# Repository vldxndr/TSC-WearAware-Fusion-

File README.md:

# InkTime - Smartwatch Project Technical Documentation

## 1. Overview
InkTime is an ultra-low-power open-hardware smartwatch designed around the nRF52840 SoC and a 1.54" E-paper display. The project focuses on extreme battery longevity, utilizing a high-efficiency dual-stage power supply and hardware-level power gating to achieve a standby target of 30 days or more.

---

## 2. System Architecture

### 2.1 Block Diagram
The system utilizes a dual-stage power topology to maximize battery discharge efficiency.

    [ USB Type-C ]     [ LiPo Battery (250mAh) ]
           | 5V VBUS          |
           v                  | BAT
    +---------------+         v
    |    BQ25180    |<--+ [MAX17048]
    |  (Charger IC) |   | (Fuel Gauge)
    +---------------+   |     |
           | VSYS       +-----+ I2C
           v                  v
    +---------------+      +-------------+
    |    RT6160     |      |             |
    | (Buck-Boost)  |      |  nRF52840   |
    +---------------+      |     MCU     |
           | 3.3V (VDD_3V3)|  (Control   |
           | System Rail   |    Hub)     |
           |               |             |
    +------+---------------+------+------+
    |      |               |      |
    |      v               |      |
    |  +-------------+     |      | SPI
    |  | PFET Switch |<--GPIO-----+      v
    |  +------+------+     |  +-------------+
    |      | VEPD          |  | 1.54" E-paper|
    |      v               |  |   Display   |
    |  +-------------+     |  +-------------+
    |  | [Display]   |     |
    |  +-------------+     | I2C Bus
    |                      |
    +---I2C==> [ BMA423 Accel ]
    |                      |
    +---I2C==> [ DRV2605L Driver ] --> [ Vibration Motor ]
    |
    |          [ PCB Antenna ] <--> [ BLE RF ]
    |
    +---GPIO-> [ User Buttons ]

---

## 3. Bill Of Materials (BOM)

| Designator | Component | Package | Manufacturer | Description |
| :--- | :--- | :--- | :--- | :--- |
| U1 | nRF52840 | aQFN-73 | Nordic Semi | SoC Bluetooth 5.0 |
| IC1 | BQ25180Y | DSBGA-8 | Texas Inst. | Li-Ion Charger w/ Power Path |
| IC9 | RT6160AWSC | WLCSP-15 | Richtek | 3.3V Buck-Boost Regulator |
| IC3 | BMA423 | LGA-12 | Bosch | Triaxial Accelerometer |
| U3 | MAX17048 | TDFN-8 | Maxim/ADI | 1-Cell Fuel Gauge |
| ANT1 | 2450AT18B100E| 1.4mm | Johanson | 2.45GHz Chip Antenna |
| J1 | 503480-2400 | FPC-24 | Molex | 0.5mm Pitch FPC Connector |
| J4 | KH-TYPE-C-16P| SMT | Kinghelm | USB Type-C 16-pin |
| Q3 | SI1308EDL | SOT-323 | Vishay | P-Channel PFET (Power Gate) |
| D3 | USBLC6-2 | SOT-23-6 | STMicro | ESD Protection |

---

## 4. Hardware Implementation Details

### 4.1 Power Management Strategy
The BQ25180 handles LiPo charging and provides the VSYS rail. This rail feeds the RT6160 Buck-Boost converter, which maintains a stable 3.3V output. This configuration is critical for longevity, as the Buck-Boost can maintain regulation even when the battery voltage drops below 3.3V, effectively utilizing the entire discharge curve of the LiPo cell.

### 4.2 Display Power Gating
To minimize parasitic leakage during deep sleep, the E-paper power rail (VEPD) is controlled via a SI1308EDL PFET high-side switch. The MCU toggles this switch via P1.01, physically disconnecting the display logic and charge pump from the power rail when no refresh cycle is active.

### 4.3 Haptic and Motion Sensing
* DRV2605L: Provides I2C-controlled haptic feedback for ERM/LRA motors with integrated waveform libraries.
* BMA423: Low-power accelerometer used for step counting and gesture recognition. It is configured to wake the MCU via a hardware interrupt on P0.08.

---

## 5. Pinout Mapping (nRF52840)

### 5.1 Communication Interfaces
* I2C (SDA/SCL): P0.06 / P0.07 (Shared bus for Charger, Fuel Gauge, Accel, and Haptics).
* SPI (Display): P0.02 (SCK), P0.03 (MOSI), P0.05 (CS), P0.15 (DC), P0.16 (RST).

### 5.2 GPIO Control Lines
* Display Busy: P0.17 (Input - monitors refresh state).
* Power Control: P1.01 (Output - PFET Enable).
* Haptic Enable: P0.12 (Output - DRV2605L EN).
* BMA Interrupt: P0.08 (Input - Motion wake-up).
* Battery Alert: P0.10 (Input - Fuel Gauge alert).
* Charger Interrupt: P0.11 (Input - Charging state change).

---

## 6. Layout Guidelines

### 6.1 RF Section
* The path from U1 Pin 55 (ANT) to ANT1 must be as short as possible.
* Maintain a 50-ohm impedance-controlled trace.
* Implement a ground keep-out zone on all layers directly beneath the ANT1 chip antenna.

### 6.2 Power Integrity
* Place the 0.47uH inductor (L7) and decoupling capacitors (22uF/10uF) as close as possible to the RT6160 (IC9) pins.
* Use wide traces for VBUS, VSYS, and VDD_3V3 to minimize voltage drops.

### 6.3 Grounding
* Utilize a solid ground plane on Layer 2.
* Stitch ground planes with multiple vias, especially near decoupling capacitors and the MCU thermal pad.

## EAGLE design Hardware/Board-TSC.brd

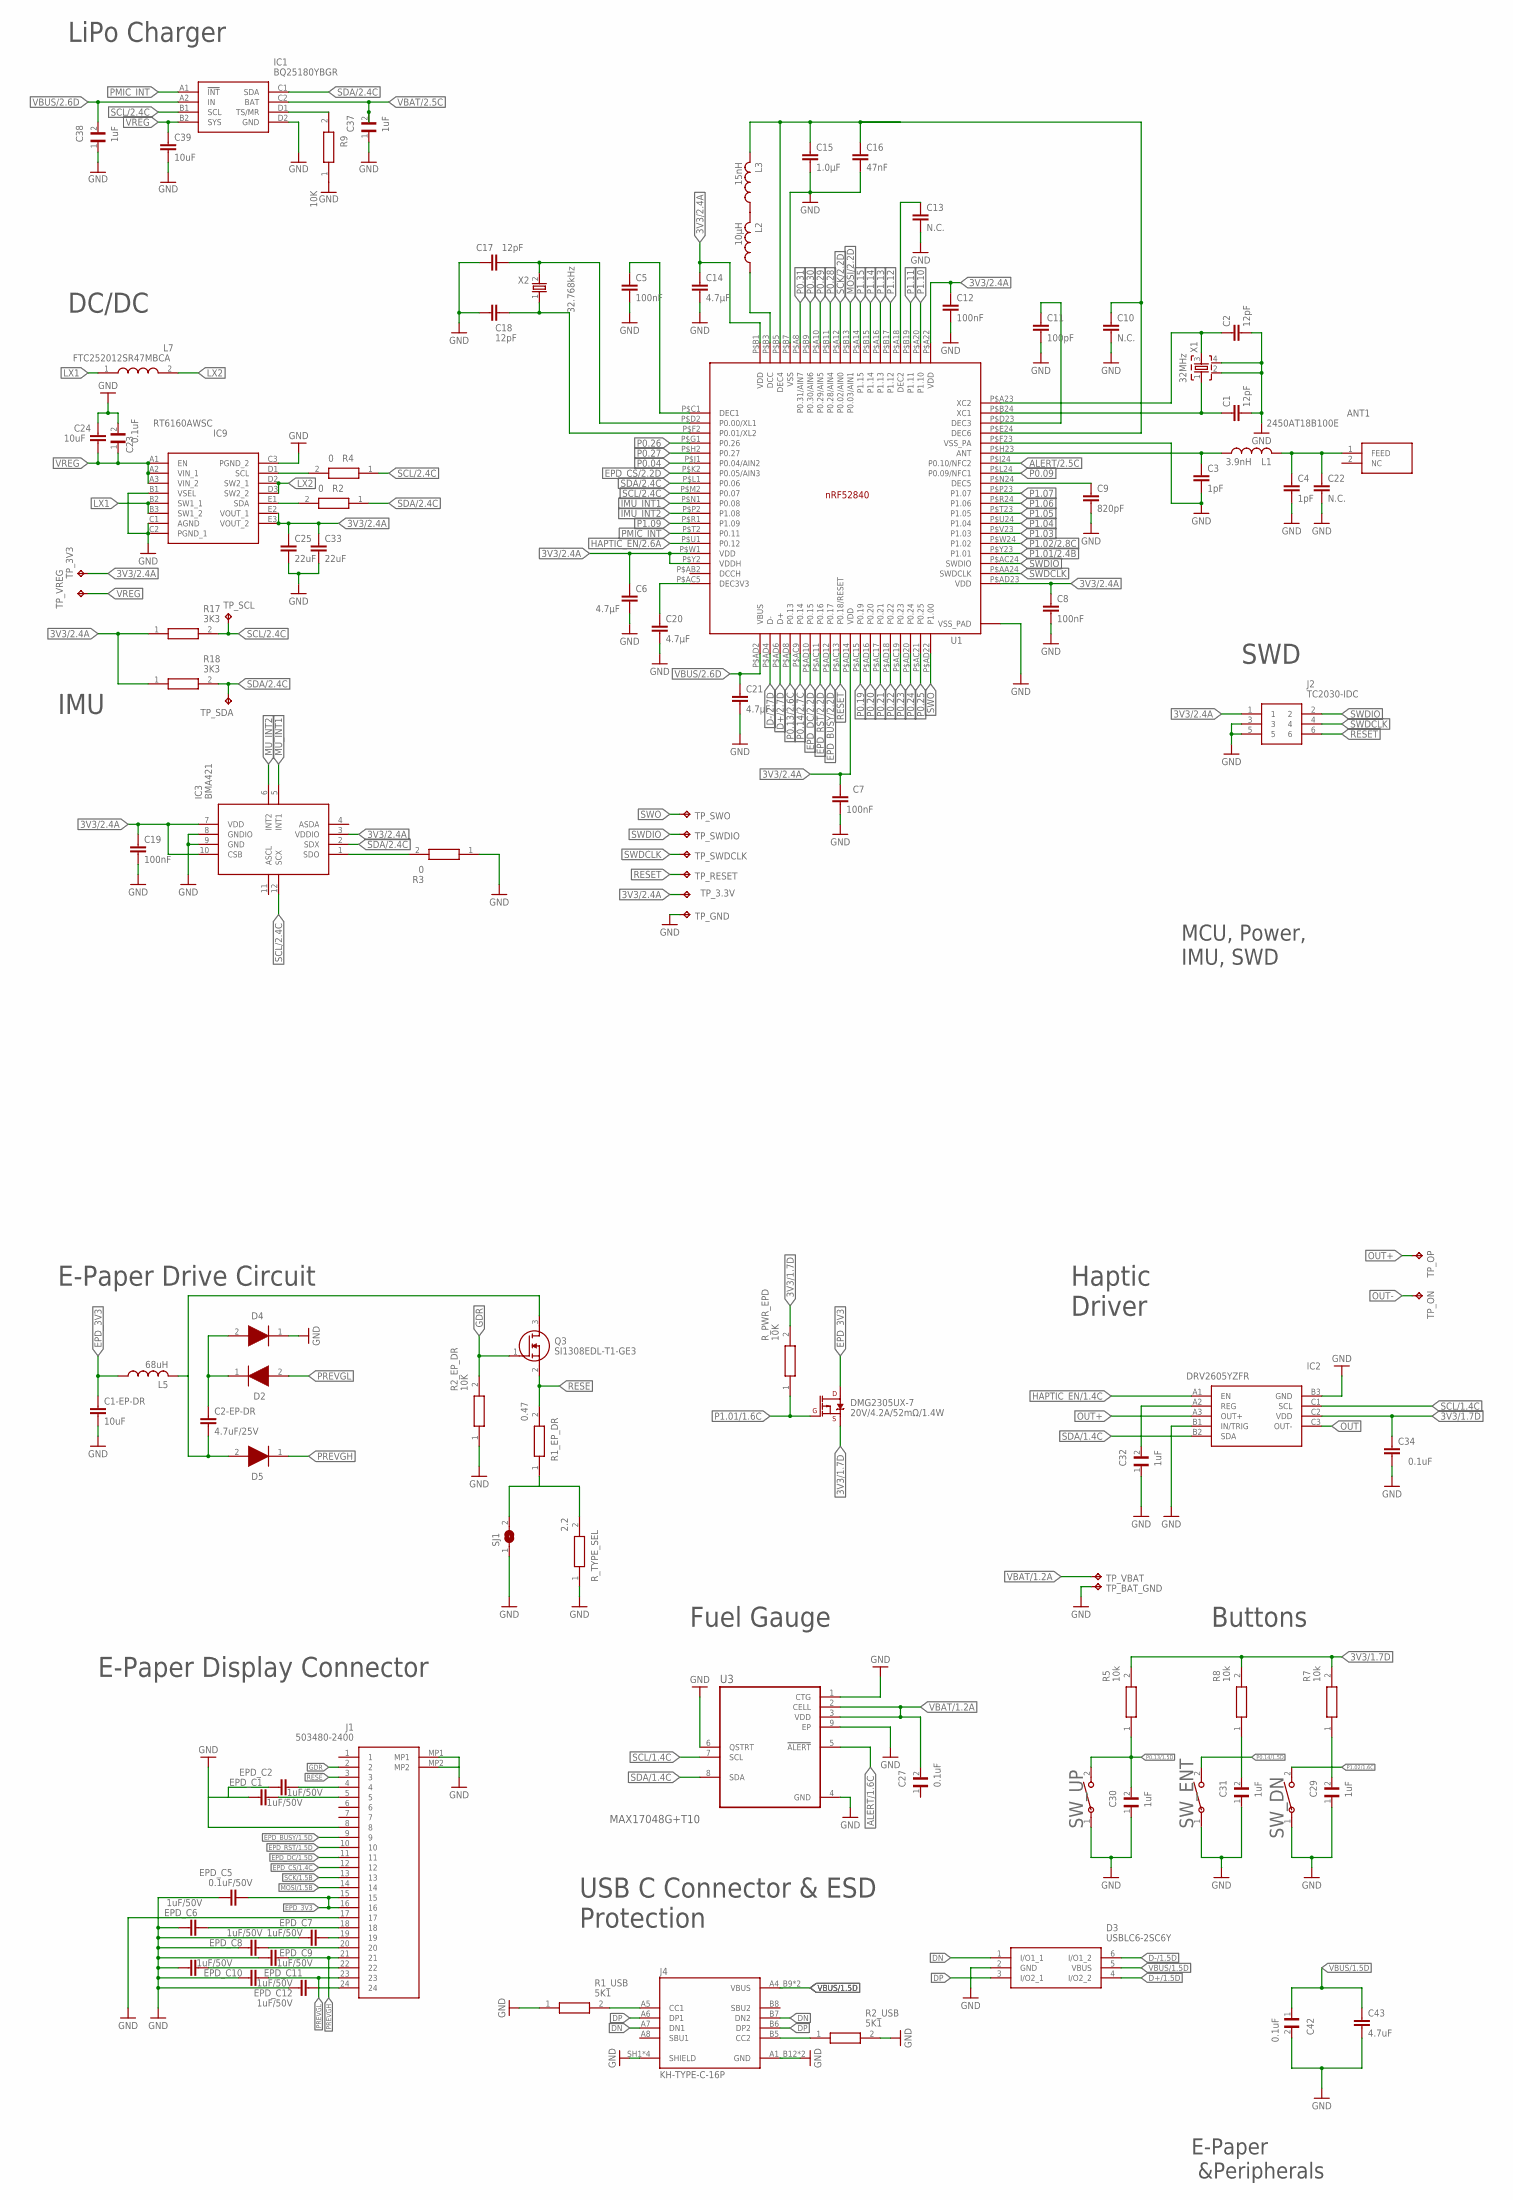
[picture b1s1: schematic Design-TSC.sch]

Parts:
ANT1: 2450AT18B100E; 2450AT18B100E_ANTC3216X140N
C1, C2, C17, C18: 12pF; NORDIC_NRF_3_RESC0201_L
C1-EP-DR, C39: 10uF; NORDIC_NRF_3_RESC0201_L
C2-EP-DR: 4.7uF/25V; NORDIC_NRF_3_RESC0201_L
C3, C4: 1pF; NORDIC_NRF_3_RESC0201_L
C5, C7, C8, C12, C19: 100nF; NORDIC_NRF_3_RESC0201_L
C6: 4.7µF; NORDIC_NRF_3_RESC0201_L
C9: 820pF; NORDIC_NRF_3_RESC0201_L
C10, C13, C22: N.C.; NORDIC_NRF_3_RESC0201_L
C11: 100pF; NORDIC_NRF_3_RESC0201_L
C14, C20, C21: 4.7µF; ESP32_C6_LIBRARY_1_ESP32_WROVER_EAGLE-LTSPICE_C0402
C15: 1.0µF; NORDIC_NRF_3_RESC0201_L
C16: 47nF; NORDIC_NRF_3_RESC0201_L
C23, C27, C42: 0.1uF; GRM011R60J152KE01L_2_CAPC0201X13N
C24: 10uF; ESP32_C6_LIBRARY_1_ESP32_WROVER_EAGLE-LTSPICE_C0402
C25, C33: 22uF; ESP32_C6_LIBRARY_1_ESP32_WROVER_EAGLE-LTSPICE_C0402
C29, C30, C31, C32, C37, C38: 1uF; GRM011R60J152KE01L_2_CAPC0201X13N
C34: 0.1uF; NORDIC_NRF_3_RESC0201_L
C43: 4.7uF; ESP32_C6_LIBRARY_1_ESP32_WROVER_EAGLE-LTSPICE_C0402
D2, D4, D5: ESP32_C6_LIBRARY_5_MBR0530; ESP32_C6_LIBRARY_5_SOD3716X135N
D3: USBLC6-2SC6Y; ESP32_C6_LIBRARY_3_SOT95P280X145-6N
DMG2305UX-7: 20V/4.2A/52mΩ/1.4W; ESP32_C6_LIBRARY_4_ESP32_C6_LIBRARY_4_ESP32_C6_LIBRARY_4_ES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
EPD_C1, EPD_C2, EPD_C6, EPD_C7, EPD_C8, EPD_C9, EPD_C10, EPD_C11, EPD_C12: 1uF/50V; ESP32_C6_LIBRARY_1_ESP32_WROVER_EAGLE-LTSPICE_C0402
EPD_C5: 0.1uF/50V; ESP32_C6_LIBRARY_1_ESP32_WROVER_EAGLE-LTSPICE_C0402
IC1: BQ25180YBGR; BQ25180YBGR_BGA8C40P2X4_100X155X50
IC2: DRV2605YZFR; DRV2605YZFR_BGA9C50P3X3_144X144X62
IC3: BMA421; BMA423_BMA423
IC9: RT6160AWSC; RT6160AWSC_BGA15C40P3X5_140X230X60
J1: 503480-2400; 503480-2400_5034802400
J2: TC2030-IDC; TC2030-IDC_TC2030IDC
J4: KH-TYPE-C-16P; KH-TYPE-C-16P_KINGHELM_KH-TYPE-C-16P
L1: 3.9nH; NORDIC_NRF_2_RESC0402_L
L2: 10µH; NORDIC_NRF_2_RESC0402_L
L3: 15nH; NORDIC_NRF_2_RESC0402_L
L5: 68uH; NORDIC_NRF_2_RESC0402_L
L7: FTC252012SR47MBCA; MLP2016SR47MT0S1_INDC2016X100N
Q3: SI1308EDL-T1-GE3; ESP32_C6_LIBRARY_6_SOT65P210X110-3N
R1_EP_DR: 0.47; ERA-1AEB3401C_0201
R1_USB: 5K1; CPF0201D7K68C1_0201
R2, R4: 0; CPF0201D7K68C1_0201
R2_EP_DR, R9: 10K; ERA-1AEB3401C_0201
R2_USB: 5K1; ERA-1AEB3401C_0201
R3: 0; ERA-1AEB3401C_0201
R5, R7, R8: 10k; CPF0201D7K68C1_0201
R17, R18: 3K3; CPF0201D7K68C1_0201
R_PWR_EPD: 10K; CPF0201D7K68C1_0201
R_TYPE_SEL: 2.2; ERA-1AEB3401C_0201
SJ1: ESP32_C6_LIBRARY_7_JUMPER_SJ
SW_DN: 2025-10-22_07-23-44_LIBRARY_EVP-AKE31ASW_EVP-AKE3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; 2025-10-22_07-23-44_LIBRARY_SW_EVP-AKE31A_PAN
SW_ENT: 2025-10-22_07-23-44_LIBRARY_EVP-AKE31ASW_EVP-AKE3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; 2025-10-22_07-23-44_LIBRARY_SW_EVP-AKE31A_PAN
SW_UP: 2025-10-22_07-23-44_LIBRARY_EVP-AKE31ASW_EVP-AKE3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; 2025-10-22_07-23-44_LIBRARY_SW_EVP-AKE31A_PAN
TP_3.3V, TP_3V3: HECTOR_WATCH_1_TPTP20R; HECTOR_WATCH_1_TP20R
TP_BAT_GND: HECTOR_WATCH_1_TPTP20R; HECTOR_WATCH_1_TP20R
TP_GND: HECTOR_WATCH_1_TPTP20R; HECTOR_WATCH_1_TP20R
TP_ON: HECTOR_WATCH_1_TPTP20R; HECTOR_WATCH_1_TP20R
TP_OP: HECTOR_WATCH_1_TPTP20R; HECTOR_WATCH_1_TP20R
TP_RESET: HECTOR_WATCH_1_TPTP20R; HECTOR_WATCH_1_TP20R
TP_SCL: HECTOR_WATCH_1_TPTP20R; HECTOR_WATCH_1_TP20R
TP_SDA: HECTOR_WATCH_1_TPTP20R; HECTOR_WATCH_1_TP20R
TP_SWDCLK: HECTOR_WATCH_1_TPTP20R; HECTOR_WATCH_1_TP20R
TP_SWDIO: HECTOR_WATCH_1_TPTP20R; HECTOR_WATCH_1_TP20R
TP_SWO: HECTOR_WATCH_1_TPTP20R; HECTOR_WATCH_1_TP20R
TP_VBAT: HECTOR_WATCH_1_TPTP20R; HECTOR_WATCH_1_TP20R
TP_VREG: HECTOR_WATCH_1_TPTP20R; HECTOR_WATCH_1_TP20R
U1: NRF52840_QF; NORDIC_NRF_4_AQFN50P700X700X85_HS-74N
U3: MAX17048G+T10; ESP32_C6_LIBRARY_SON50P200X200X80-9N
X1: 32MHz; NORDIC_NRF_BT-XTAL_2016_N
X2: 32.768kHz; NORDIC_NRF_1_XTAL_3215_N

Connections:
3V3/1.7D: C34.1, DMG2305UX-7.2 (S), IC2.C2 (VDD), R5.2, R7.2, R8.2, R_PWR_EPD.2
3V3/2.4A: C6.1, C7.1, C8.1, C12.1, C14.1, C19.1, C25.1, C33.1, IC3.3 (VDDIO), IC3.7 (VDD), IC3.10 (CSB), IC9.E2 (VOUT_1), IC9.E3 (VOUT_2), J2.1, R17.1, R18.1, TP_3.3V.TP, TP_3V3.TP, U1.P$A22 (VDD), U1.P$AD14 (VDD), U1.P$AD23 (VDD), U1.P$B1 (VDD), U1.P$W1 (VDD), U1.P$Y2 (VDDH)
ALERT/1.6C: U3.5 (!ALERT)
ALERT/2.5C: U1.P$J24 (P0.10/NFC2)
D+/1.5D: D3.4 (I/O2_2)
D+/2.7D: U1.P$AD6 (D+)
D-/1.5D: D3.6 (I/O1_2)
D-/2.7D: U1.P$AD4 (D-)
DN: D3.1 (I/O1_1), J4.A7 (DN1), J4.B7 (DN2)
DP: D3.3 (I/O2_1), J4.A6 (DP1), J4.B6 (DP2)
EPD_3V3: C1-EP-DR.1, DMG2305UX-7.3 (D), EPD_C5.2, J1.15, J1.16, L5.1
EPD_BUSY/1.5D: J1.9
EPD_BUSY/2.2D: U1.P$AD12 (P0.17)
EPD_CS/1.4C: J1.12
EPD_CS/2.2D: U1.P$K2 (P0.05/AIN3)
EPD_DC/1.5D: J1.11
EPD_DC/2.2D: U1.P$AD10 (P0.15)
EPD_RST/1.5D: J1.10
EPD_RST/2.2D: U1.P$AC11 (P0.16)
GDR: J1.2, Q3.1 (G), R2_EP_DR.2
GND: C1.2, C1-EP-DR.2, C2.2, C3.2, C4.2, C5.2, C6.2, C7.2, C8.2, C9.2, C10.2, C11.2, C12.2, C13.2, C14.2, C15.2, C16.2, C17.1, C18.2, C19.2, C20.2, C21.2, C22.2, C23.2, C24.1, C25.2, C29.1, C30.1, C31.1, C32.1, C33.2, C34.2, C37.1, C38.1, C39.2, C42.2, C43.2, D3.2 (GND), D4.1 (K), EPD_C5.1, EPD_C6.1, EPD_C7.1, EPD_C8.1, EPD_C9.1, EPD_C10.1, EPD_C11.1, EPD_C12.1, IC1.D2 (GND), IC2.B1 (IN/TRIG), IC2.B3 (GND), IC3.8 (GNDIO), IC3.9 (GND), IC9.B1 (VSEL), IC9.C1 (AGND), IC9.C2 (PGND_1), IC9.C3 (PGND_2), J1.8, J1.17, J1.MP1, J2.3, J2.5, J4.A1_B12 (GND), J4.A12_B1 (GND), J4.SH1 (SHIELD), J4.SH2 (SHIELD), J4.SH3 (SHIELD), J4.SH4 (SHIELD), R1_USB.1, R2_EP_DR.1, R2_USB.2, R3.1, R9.1, R_TYPE_SEL.1, SJ1.1, SW_DN.1, SW_ENT.1, SW_UP.1, TP_BAT_GND.TP, TP_GND.TP, U1.P$74 (VSS_PAD), U1.P$75 (VSS_PAD), U1.P$76 (VSS_PAD), U1.P$77 (VSS_PAD), U1.P$78 (VSS_PAD), U1.P$79 (VSS_PAD), U1.P$80 (VSS_PAD), U1.P$81 (VSS_PAD), U1.P$82 (VSS_PAD), U1.P$83 (VSS_PAD), U1.P$84 (VSS_PAD), U1.P$85 (VSS_PAD), U1.P$86 (VSS_PAD), U1.P$87 (VSS_PAD), U1.P$88 (VSS_PAD), U1.P$89 (VSS_PAD), U1.P$90 (VSS_PAD), U1.P$B7 (VSS), U1.P$F23 (VSS_PA), U3.1 (CTG), U3.4 (GND), U3.6 (QSTRT), U3.9 (EP), X1.2, X1.4
HAPTIC_EN/1.4C: IC2.A1 (EN)
HAPTIC_EN/2.6A: U1.P$U1 (P0.12)
IMU_INT1: U1.P$N1 (P0.08)
IMU_INT2: U1.P$P2 (P1.08)
JJ: C10.1, C15.1, C16.1, L3.2, U1.P$B5 (DEC4), U1.P$E24 (DEC6)
LX1: IC9.B2 (SW1_1), IC9.B3 (SW1_2), L7.1
LX2: IC9.D2 (SW2_1), IC9.D3 (SW2_2), L7.2
MOSI/1.5B: J1.14
MOSI/2.2D: U1.P$B13 (P0.03/AIN1)
MU_INT1: IC3.5 (INT1)
MU_INT2: IC3.6 (INT2)
unnamed: IC1.D1 (TS/MR), R9.2
unnamed: IC9.D1 (SCL), R4.2
unnamed: IC9.E1 (SDA), R2.2
unnamed: IC3.1 (SDO), R3.2
unnamed: C20.1, U1.P$AC5 (DEC3V3)
unnamed: C18.1, U1.P$F2 (P0.01/XL2), X2.1
unnamed: C17.2, U1.P$D2 (P0.00/XL1), X2.2
unnamed: C5.1, U1.P$C1 (DEC1)
unnamed: C9.1, U1.P$N24 (DEC5)
unnamed: L2.1, U1.P$B3 (DCC)
unnamed: L2.2, L3.1
unnamed: C3.1, L1.1, U1.P$H23 (ANT)
unnamed: ANT1.1 (FEED), C4.1, C22.1, L1.2
unnamed: C11.1, U1.P$D23 (DEC3)
unnamed: C2.1, U1.P$A23 (XC2), X1.3
unnamed: C1.1, U1.P$B24 (XC1), X1.1
unnamed: C2-EP-DR.2, D5.2 (A), L5.2, Q3.3 (D)
unnamed: C2-EP-DR.1, D2.1 (K), D4.2 (A)
unnamed: R1_EP_DR.1, R_TYPE_SEL.2, SJ1.2
unnamed: C13.1, U1.P$A18 (DEC2)
unnamed: C32.2, IC2.A2 (REG)
unnamed: EPD_C2.2, J1.4
unnamed: EPD_C1.2, J1.5
unnamed: EPD_C6.2, J1.18
unnamed: EPD_C7.2, J1.19
unnamed: EPD_C8.2, J1.20
unnamed: J4.A5 (CC1), R1_USB.2
unnamed: EPD_C10.2, J1.22
unnamed: C31.2, R8.1
unnamed: EPD_C12.2, J1.24
unnamed: J4.B5 (CC2), R2_USB.1
unnamed: C29.2, R7.1
OUT: IC2.C3 (OUT-)
OUT+: IC2.A3 (OUT+), TP_OP.TP
OUT-: TP_ON.TP
P0.04: U1.P$J1 (P0.04/AIN2)
P0.09: U1.P$L24 (P0.09/NFC1)
P0.13/1.5D: C30.2, R5.1, SW_UP.2
P0.13/2.6C: U1.P$AD8 (P0.13)
P0.14/1.5D: SW_ENT.2
P0.14/2.7C: U1.P$AC9 (P0.14)
P0.19: U1.P$AC15 (P0.19)
P0.20: U1.P$AD16 (P0.20)
P0.21: U1.P$AC17 (P0.21)
P0.22: U1.P$AD18 (P0.22)
P0.23: U1.P$AC19 (P0.23)
P0.24: U1.P$AD20 (P0.24)
P0.25: U1.P$AC21 (P0.25)
P0.26: U1.P$G1 (P0.26)
P0.27: U1.P$H2 (P0.27)
P0.28: U1.P$B11 (P0.28/AIN4)
P0.29: U1.P$A10 (P0.29/AIN5)
P0.30: U1.P$B9 (P0.30/AIN6)
P0.31: U1.P$A8 (P0.31/AIN7)
P1.01/1.6C: DMG2305UX-7.1 (G), R_PWR_EPD.1
P1.01/2.4B: U1.P$Y23 (P1.01)
P1.02/1.6C: SW_DN.2
P1.02/2.8C: U1.P$W24 (P1.02)
P1.03: U1.P$V23 (P1.03)
P1.04: U1.P$U24 (P1.04)
P1.05: U1.P$T23 (P1.05)
P1.06: U1.P$R24 (P1.06)
P1.07: U1.P$P23 (P1.07)
P1.09: U1.P$R1 (P1.09)
P1.10: U1.P$A20 (P1.10)
P1.11: U1.P$B19 (P1.11)
P1.12: U1.P$B17 (P1.12)
P1.13: U1.P$A16 (P1.13)
P1.14: U1.P$B15 (P1.14)
P1.15: U1.P$A14 (P1.15)
PMIC_INT: IC1.A1 (!INT), U1.P$T2 (P0.11)
PREVGH: D5.1 (K), EPD_C9.2, J1.21
PREVGL: D2.2 (A), EPD_C11.2, J1.23
RESE: J1.3, Q3.2 (S), R1_EP_DR.2
RESET: J2.6, TP_RESET.TP, U1.P$AC13 (P0.18/RESET)
SCK/1.5B: J1.13
SCK/2.2D: U1.P$A12 (P0.02/AIN0)
SCL/1.4C: IC2.C1 (SCL), U3.7 (SCL)
SCL/2.4C: IC1.B1 (SCL), IC3.12 (SCX), R4.1, R17.2, TP_SCL.TP, U1.P$M2 (P0.07)
SDA/1.4C: IC2.B2 (SDA), U3.8 (SDA)
SDA/2.4C: IC1.C1 (SDA), IC3.2 (SDX), R2.1, R18.2, TP_SDA.TP, U1.P$L1 (P0.06)
SWDCLK: J2.4, TP_SWDCLK.TP, U1.P$AA24 (SWDCLK)
SWDIO: J2.2, TP_SWDIO.TP, U1.P$AC24 (SWDIO)
SWO: TP_SWO.TP, U1.P$AD22 (P1.00)
VBAT/1.2A: C27.2, TP_VBAT.TP, U3.2 (CELL), U3.3 (VDD)
VBAT/2.5C: C37.2, IC1.C2 (BAT)
VBUS/1.5D: C42.1, C43.1, D3.5 (VBUS), J4.A4_B9 (VBUS), J4.A9_B4 (VBUS)
VBUS/2.6D: C21.1, C38.2, IC1.A2 (IN), U1.P$AD2 (VBUS)
VREG: C23.1, C24.2, C39.1, IC1.B2 (SYS), IC9.A1 (EN), IC9.A2 (VIN_1), IC9.A3 (VIN_2), TP_VREG.TP

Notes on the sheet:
LiPo Charger
DC/DC
IMU
SWD
MCU, Power, IMU, SWD
E-Paper Drive Circuit
Haptic Driver
E-Paper Display Connector
Fuel Gauge
Buttons
E-Paper &Peripherals
USB C Connector & ESD Protection

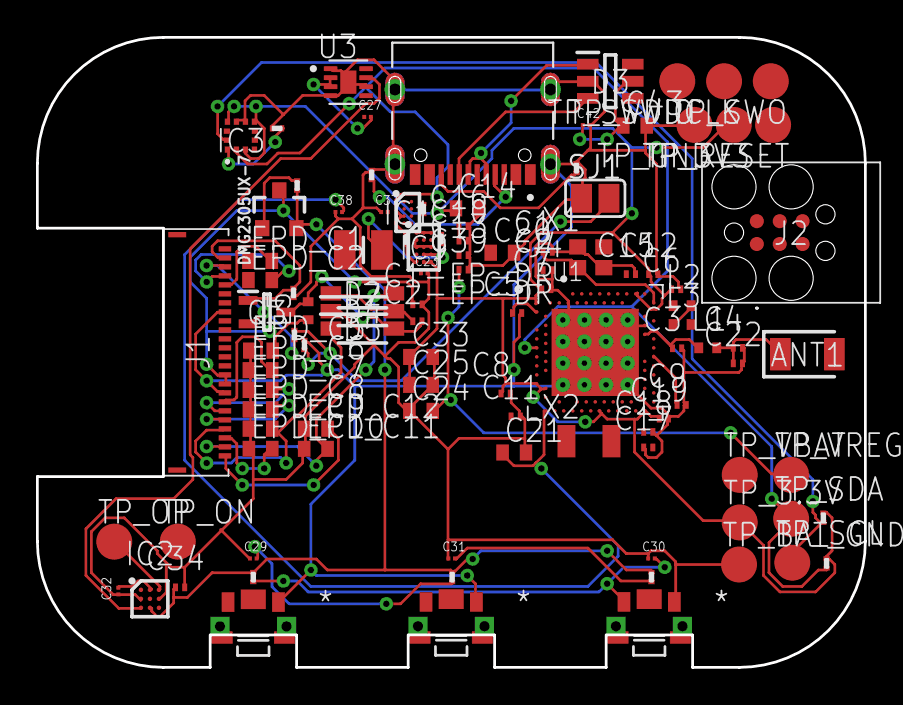
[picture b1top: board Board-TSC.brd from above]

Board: 4 copper layers, 46.0 x 35.0 mm, 105 parts (0 on the bottom side), 62 nets.

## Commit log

2026-04-10 Add LICENSE file with MIT License text
2026-04-10 Add MIT License to the project
2026-04-10 Delete
2026-04-10 Revise README for improved technical clarity

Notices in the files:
parts and their libraries:
COPYRIGHT: Copyright (C) 2025 Ultra Librarian. All rights reserved.
